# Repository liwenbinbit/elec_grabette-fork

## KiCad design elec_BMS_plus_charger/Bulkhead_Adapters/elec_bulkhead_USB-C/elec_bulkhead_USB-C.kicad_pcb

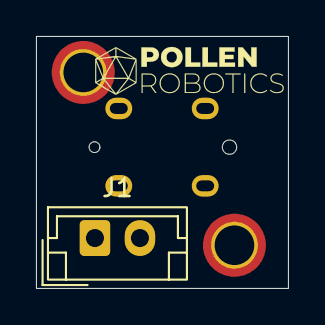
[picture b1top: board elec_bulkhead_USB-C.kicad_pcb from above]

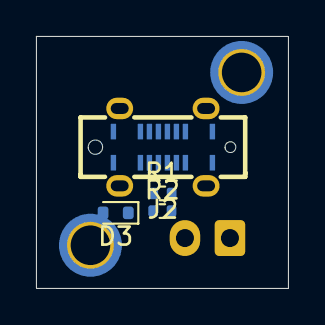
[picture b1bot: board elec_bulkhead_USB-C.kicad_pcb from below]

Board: 2 copper layers, 14.0 x 14.0 mm, 9 parts (4 on the bottom side), 4 nets, no tracks yet.

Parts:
D3: ESD5Z6.0; D_SOD-523
H2: Logo HF 2025; Logo_HF_2025
H3: DNP Logo Pollen 2021; Logo_Pollen_2021_sq
H4, H5: Mounting Holes M2; MountingHole_2.2mm_M2_ISO7380_Pad_TopBottom
J1: JST EH 2; JST_EH_B2B-EH-A_1x02_P2.50mm_Vertical
J2: USB-C Rec. Vert.; USB-C_16p_vert_Shou-Han_TYPE-C 16P LTH6.8 - C5187468
R1, R2: 5k1; R_0402_1005Metric

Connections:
GND: D3.2 (A), H4.1, H5.1, J1.1, J2.A1 (GND), J2.A12 (GND), J2.B1 (GND), J2.B12 (GND), J2.S1 (SHIELD), R1.2, R2.2
unnamed: D3.1 (K), J1.2, J2.A4 (VBUS), J2.A9 (VBUS), J2.B4 (VBUS), J2.B9 (VBUS)
unnamed: J2.A5 (CC1), R1.1
unnamed: J2.B5 (CC2), R2.1

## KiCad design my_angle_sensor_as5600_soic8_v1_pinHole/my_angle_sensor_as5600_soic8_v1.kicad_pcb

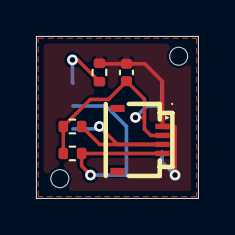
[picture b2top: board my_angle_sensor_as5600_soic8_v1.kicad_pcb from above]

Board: 2 copper layers, 9.0 x 9.0 mm, 8 parts (1 on the bottom side), 5 nets.

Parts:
C1: 100n; C_0402_1005Metric
H1, H2: MountingHole; LocatingHole_NPTH_D1.0
J1: HC-FPC-05-09-4RLTAG; FPC-SMD_4P-P0.50_HC-FPC-05-09-4RLTAG
R1: 0R; R_0402_1005Metric
R2, R3: 10k; R_0402_1005Metric
U1: AS5600L; SOIC-8_3.9x4.9mm_P1.27mm

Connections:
+3V3: C1.1, J1.2, R2.1, R3.1, U1.1 (Vdd5V), U1.2 (Vdd3V3)
/SCL: J1.4, R3.2, U1.7 (SCL)
/SDA: J1.3, R2.2, U1.6 (SDA)
GND: C1.2, J1.1, R1.2, U1.4 (Gnd)
unnamed: R1.1, U1.8 (Dir)

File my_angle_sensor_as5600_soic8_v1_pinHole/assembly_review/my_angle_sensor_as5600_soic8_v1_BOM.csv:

"Reference","Qty","Value","DNP","Exclude from BOM","Exclude from Board","Exclude from Simulation","Footprint","Datasheet","LCSC Part"
"C1","1","100n","","","","","Capacitor_SMD:C_0402_1005Metric","","C307331"
"J1","1","HC-FPC-05-09-4RLTAG","","","","","GloveMini_Connectors:FPC-SMD_4P-P0.50_HC-FPC-05-09-4RLTAG","","C5213746"
"R1","1","0R","","","","","Resistor_SMD:R_0402_1005Metric","","C17168"
"U1","1","AS5600L","","","","","Package_SO:SOIC-8_3.9x4.9mm_P1.27mm","","C2153666"
